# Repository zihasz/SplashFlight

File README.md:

# SplashFlight

SplashFlight is an all-in-one UAV control system designed from scratch, including a quadcopter control board, a general UAV control board, and software.

## Progress

### Hardware

-   [x] General UAV control board
-   [x] Quad-copter control board
-   [ ] PWM extension board
-   [ ] RF extension board
-   [ ] USB dongle - GPS
-   [ ] USB dongle - RF

### Software

-   [ ] Firmware for general UAV board
-   [ ] Firmware for quad-copter board
-   [ ] Ground control station software
-   [ ] Multi-OS Drivers for USB dongles

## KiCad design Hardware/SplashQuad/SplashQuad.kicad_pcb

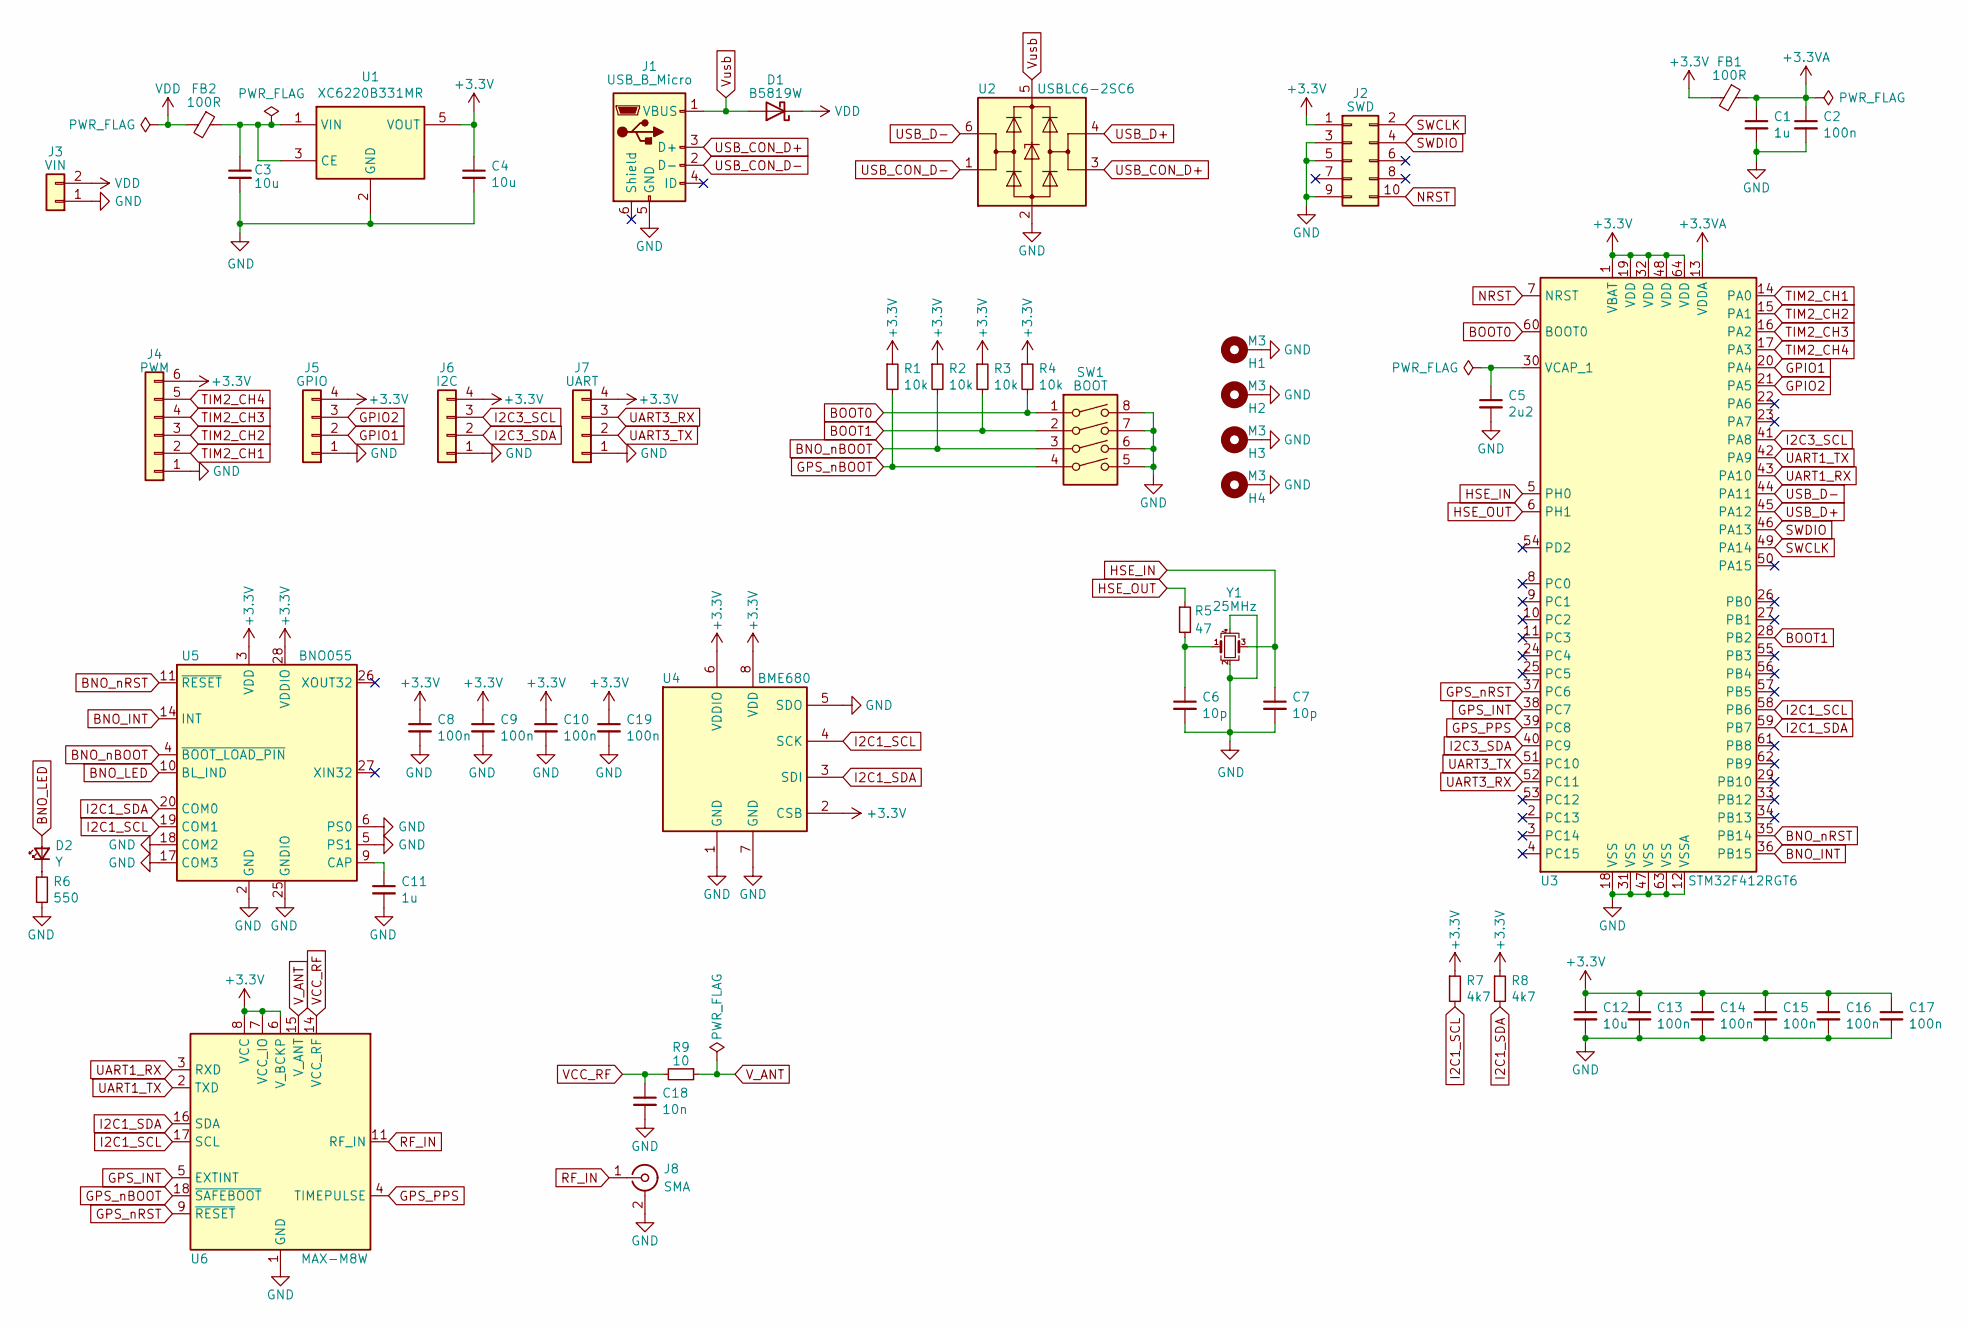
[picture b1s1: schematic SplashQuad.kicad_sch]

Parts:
C1, C11: 1u; C_0402_1005Metric
C2, C8, C9, C10, C13, C14, C15, C16, C17, C19: 100n; C_0402_1005Metric
C3, C4, C12: 10u; C_0402_1005Metric
C5: 2u2; C_0402_1005Metric
C6, C7: 10p; C_0402_1005Metric
C18: 10n; C_0402_1005Metric
D1: B5819W; D_SOD-123
D2: Y; LED_0603_1608Metric
FB1, FB2: 100R; L_0603_1608Metric
H1, H2, H3, H4: M3; MountingHole_3.2mm_M3_Pad_Via
J1: USB_B_Micro; USB_Micro-B_Molex-105017-0001
J2: SWD; PinHeader_2x05_P1.27mm_Vertical
J3: VIN; Molex_PicoBlade_53048-0210_1x02_P1.25mm_Horizontal
J4: PWM; Molex_PicoBlade_53048-0610_1x06_P1.25mm_Horizontal
J5: GPIO; Molex_PicoBlade_53048-0410_1x04_P1.25mm_Horizontal
J6: I2C; Molex_PicoBlade_53048-0410_1x04_P1.25mm_Horizontal
J7: UART; Molex_PicoBlade_53048-0410_1x04_P1.25mm_Horizontal
J8: SMA; SMA_Samtec_SMA-J-P-X-ST-EM1_EdgeMount
R1, R2, R3, R4: 10k; R_0402_1005Metric
R5: 47; R_0402_1005Metric
R6: 550; R_0402_1005Metric
R7, R8: 4k7; R_0402_1005Metric
R9: 10; R_0402_1005Metric
SW1: BOOT; SW_DIP_SPSTx04_Slide_Omron_A6H-4101_W6.15mm_P1.27mm
U1: XC6220B331MR; SOT-23-5
U2: USBLC6-2SC6; SOT-23-6
U3: STM32F412RGT6; LQFP-64_10x10mm_P0.5mm
U4: BME680; Bosch_LGA-8_3x3mm_P0.8mm_ClockwisePinNumbering
U5: BNO055; LGA-28_5.2x3.8mm_P0.5mm
U6: MAX-M8W; ublox_MAX
Y1: 25MHz; Crystal_SMD_3225-4Pin_3.2x2.5mm

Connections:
+3.3VA: C1.1, C2.1, FB1.1, U3.13 (VDDA)
+3V3: C4.1, C8.1, C9.1, C10.1, C12.1, C13.1, C14.1, C15.1, C16.1, C17.1, C19.1, FB1.2, J2.1, J4.6, J5.4, J6.4, J7.4, R1.1, R2.1, R3.1, R4.1, R7.1, R8.1, U1.5 (VOUT), U3.1 (VBAT), U3.19 (VDD), U3.32 (VDD), U3.48 (VDD), U3.64 (VDD), U4.2 (CSB), U4.6 (VDDIO), U4.8 (VDD), U5.3 (VDD), U5.28 (VDDIO), U6.6 (V_BCKP), U6.7 (VCC_IO), U6.8 (VCC)
BNO_INT: U3.36 (PB15), U5.14 (INT)
BNO_LED: D2.2 (A), U5.10 (BL_IND)
BNO_nBOOT: R2.2, SW1.3, U5.4 (~BOOT_LOAD_PIN)
BNO_nRST: U3.35 (PB14), U5.11 (~RESET)
BOOT0: R4.2, SW1.1, U3.60 (BOOT0)
BOOT1: R3.2, SW1.2, U3.28 (PB2)
GND: C1.2, C2.2, C3.2, C4.2, C5.2, C6.2, C7.2, C8.2, C9.2, C10.2, C11.2, C12.2, C13.2, C14.2, C15.2, C16.2, C17.2, C18.2, C19.2, H1.1, H2.1, H3.1, H4.1, J1.5 (GND), J2.3, J2.5, J2.9, J3.1, J4.1, J5.1, J6.1, J7.1, J8.2 (Ext), R6.2, SW1.5, SW1.6, SW1.7, SW1.8, U1.2 (GND), U2.2 (GND), U3.12 (VSSA), U3.18 (VSS), U3.31 (VSS), U3.47 (VSS), U3.63 (VSS), U4.1 (GND), U4.5 (SDO), U4.7 (GND), U5.2 (GND), U5.5 (PS1), U5.6 (PS0), U5.15 (GNDIO), U5.16 (GNDIO), U5.17 (COM3), U5.18 (COM2), U5.25 (GNDIO), U6.1 (GND), U6.10 (GND), U6.12 (GND), Y1.2, Y1.4
GPIO1: J5.2, U3.20 (PA4)
GPIO2: J5.3, U3.21 (PA5)
GPS_INT: U3.38 (PC7), U6.5 (EXTINT)
GPS_PPS: U3.39 (PC8), U6.4 (TIMEPULSE)
GPS_nBOOT: R1.2, SW1.4, U6.18 (~SAFEBOOT)
GPS_nRST: U3.37 (PC6), U6.9 (~RESET)
HSE_IN: C7.1, U3.5 (PH0), Y1.3
HSE_OUT: R5.1, U3.6 (PH1)
I2C1_SCL: R7.2, U3.58 (PB6), U4.4 (SCK), U5.19 (COM1), U6.17 (SCL)
I2C1_SDA: R8.2, U3.59 (PB7), U4.3 (SDI), U5.20 (COM0), U6.16 (SDA)
I2C3_SCL: J6.3, U3.41 (PA8)
I2C3_SDA: J6.2, U3.40 (PC9)
NRST: J2.10, U3.7 (NRST)
unnamed: C3.1, FB2.1, U1.1 (VIN), U1.3 (CE)
unnamed: C5.1, U3.30 (VCAP_1)
unnamed: C6.1, R5.2, Y1.1
unnamed: C11.1, U5.9 (CAP)
unnamed: D2.1 (K), R6.1
RF_IN: J8.1 (In), U6.11 (RF_IN)
SWCLK: J2.2, U3.49 (PA14)
SWDIO: J2.4, U3.46 (PA13)
TIM2_CH1: J4.2, U3.14 (PA0)
TIM2_CH2: J4.3, U3.15 (PA1)
TIM2_CH3: J4.4, U3.16 (PA2)
TIM2_CH4: J4.5, U3.17 (PA3)
UART1_RX: U3.43 (PA10), U6.3 (RXD)
UART1_TX: U3.42 (PA9), U6.2 (TXD)
UART3_RX: J7.3, U3.52 (PC11)
UART3_TX: J7.2, U3.51 (PC10)
USB_CON_D+: J1.3 (D+), U2.3 (I/O2)
USB_CON_D-: J1.2 (D-), U2.1 (I/O1)
USB_D+: U2.4 (I/O2), U3.45 (PA12)
USB_D-: U2.6 (I/O1), U3.44 (PA11)
VCC_RF: C18.1, R9.2, U6.14 (VCC_RF)
VDD: D1.1 (K), FB2.2, J3.2
V_ANT: R9.1, U6.15 (V_ANT)
Vusb: D1.2 (A), J1.1 (VBUS), U2.5 (VBUS)

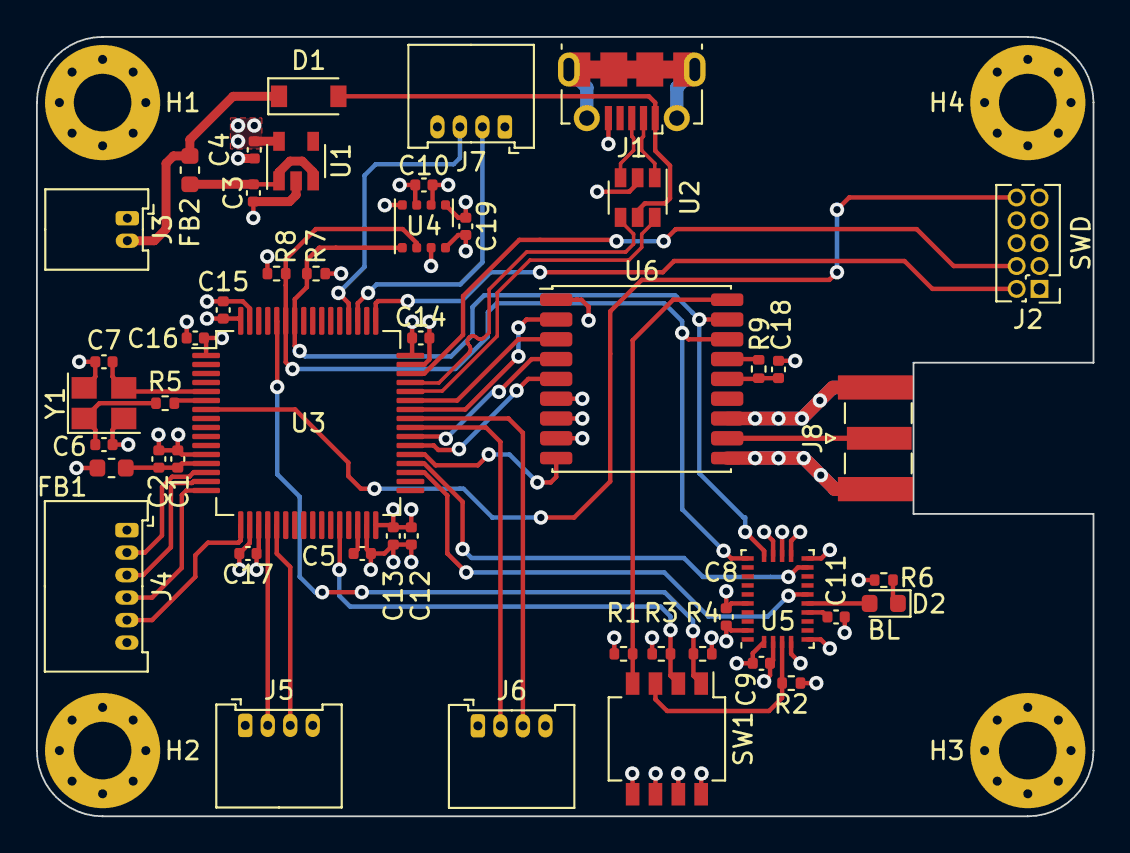
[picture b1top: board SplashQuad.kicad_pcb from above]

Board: 4 copper layers, 58.7 x 43.3 mm, 52 parts (0 on the bottom side), 46 nets.

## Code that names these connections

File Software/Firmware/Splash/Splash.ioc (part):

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Mcu.Name=STM32H753VITx
Mcu.Package=LQFP100
Mcu.UserName=STM32H753VITx
PA0.Mode=IN16-Differential
PA0.Signal=ADC1_INP16
PA1.Mode=IN16-Differential
PA1.Signal=ADC1_INN16
PA11.GPIOParameters=GPIO_Label
PA11.GPIO_Label=USB_DN
PA11.Mode=Device_Only
PA11.Signal=USB_OTG_FS_DM
PA12.GPIOParameters=GPIO_Label
PA12.GPIO_Label=USB_DP
PA12.Mode=Device_Only
PA12.Signal=USB_OTG_FS_DP
PA13\ (JTMS/SWDIO).GPIOParameters=GPIO_Label
PA13\ (JTMS/SWDIO).GPIO_Label=SWDIO
PA13\ (JTMS/SWDIO).Mode=Serial_Wire
PA13\ (JTMS/SWDIO).Signal=DEBUG_JTMS-SWDIO
PA14\ (JTCK/SWCLK).GPIOParameters=GPIO_Label
PA14\ (JTCK/SWCLK).GPIO_Label=SWCLK
PA14\ (JTCK/SWCLK).Mode=Serial_Wire
PA14\ (JTCK/SWCLK).Signal=DEBUG_JTCK-SWCLK
PA2.Signal=ADCx_INP14
PA3.Signal=ADCx_INP15
PA4.Signal=COMP_DAC11_group
PA5.Signal=COMP_DAC12_group
PA8.Mode=I2C
PA8.Signal=I2C3_SCL
PB10.Mode=I2C
PB10.Signal=I2C2_SCL
PB11.Mode=I2C
PB11.Signal=I2C2_SDA
PB12.Mode=Asynchronous
PB12.Signal=UART5_RX
PB13.Mode=Asynchronous
PB13.Signal=UART5_TX
PB14.Mode=Multiprocessor_communication
PB14.Signal=USART1_TX
PB15.Mode=Multiprocessor_communication
PB15.Signal=USART1_RX
PB3\ (JTDO/TRACESWO).Mode=Full_Duplex_Master
PB3\ (JTDO/TRACESWO).Signal=SPI1_SCK
PB4\ (NJTRST).Mode=Full_Duplex_Master
PB4\ (NJTRST).Signal=SPI1_MISO
PB5.Mode=Full_Duplex_Master
PB5.Signal=SPI1_MOSI
PB6.GPIOParameters=GPIO_Label
PB6.GPIO_Label=BME_nCS
PB6.Signal=GPIO_Output
PB7.GPIOParameters=GPIO_Label
PB7.GPIO_Label=ADC_nCS
PB7.Signal=GPIO_Output
PB8.Mode=I2C
PB8.Signal=I2C1_SCL
PB9.Mode=I2C
PB9.Signal=I2C1_SDA
PC10.Mode=Asynchronous
PC10.Signal=UART4_TX
PC11.Mode=Asynchronous
PC11.Signal=UART4_RX
PC3_C.Signal=SPI2_MOSI
PC6.Mode=Asynchronous
PC6.Signal=USART6_TX
PC7.Mode=Asynchronous
PC7.Signal=USART6_RX
PC9.Mode=I2C
PC9.Signal=I2C3_SDA
PD1.Signal=GPIO_Input
PD12.Mode=I2C
PD12.Signal=I2C4_SCL
PD13.Mode=I2C
PD13.Signal=I2C4_SDA
PD2.Signal=GPIO_Input
PD3.Signal=GPIO_Output
PD4.Signal=GPIO_Output
PD5.Mode=Asynchronous
PD5.Signal=USART2_TX
PD6.Mode=Asynchronous
PD6.Signal=USART2_RX
PD7.GPIOParameters=GPIO_Label
PD7.GPIO_Label=ADC_nDRDY
PD7.Signal=GPIO_Input
PD8.Mode=Asynchronous
PD8.Signal=USART3_TX
PD9.Mode=Asynchronous
PD9.Signal=USART3_RX
PE0.GPIOParameters=GPIO_Label
PE0.GPIO_Label=IMU_INT
PE0.Signal=GPIO_Output
PE1.GPIOParameters=GPIO_Label
PE1.GPIO_Label=IMU_nRST
PE1.Signal=GPIO_Output
PE11.Signal=S_TIM1_CH2
PE13.Signal=S_TIM1_CH3
PE14.Signal=S_TIM1_CH4
PE7.Mode=Asynchronous
PE7.Signal=UART7_RX
PE8.Mode=Asynchronous
PE8.Signal=UART7_TX
PE9.Signal=S_TIM1_CH1
PH0-OSC_IN\ (PH0).GPIOParameters=GPIO_Label
PH0-OSC_IN\ (PH0).GPIO_Label=HSE_IN
PH0-OSC_IN\ (PH0).Mode=HSE-External-Oscillator
PH0-OSC_IN\ (PH0).Signal=RCC_OSC_IN
PH1-OSC_OUT\ (PH1).GPIOParameters=GPIO_Label
PH1-OSC_OUT\ (PH1).GPIO_Label=HSE_OUT
PH1-OSC_OUT\ (PH1).Mode=HSE-External-Oscillator
PH1-OSC_OUT\ (PH1).Signal=RCC_OSC_OUT
RCC.HSE_VALUE=16000000
RCC.SYSCLKFreq_VALUE=64000000
board=custom

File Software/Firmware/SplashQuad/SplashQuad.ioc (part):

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Mcu.Name=STM32F412R(E-G)Tx
Mcu.Package=LQFP64
Mcu.UserName=STM32F412RGTx
PA0.Signal=S_TIM2_CH1_ETR
PA1.Signal=S_TIM2_CH2
PA10.Mode=Asynchronous
PA10.Signal=USART1_RX
PA11.Mode=Device_Only
PA11.Signal=USB_OTG_FS_DM
PA12.Mode=Device_Only
PA12.Signal=USB_OTG_FS_DP
PA13.Mode=Serial_Wire
PA13.Signal=SYS_JTMS-SWDIO
PA14.Mode=Serial_Wire
PA14.Signal=SYS_JTCK-SWCLK
PA2.Signal=S_TIM2_CH3
PA3.Signal=S_TIM2_CH4
PA4.Signal=ADCx_IN4
PA5.Signal=ADCx_IN5
PA8.Mode=I2C
PA8.Signal=I2C3_SCL
PA9.Mode=Asynchronous
PA9.Signal=USART1_TX
PB6.Mode=I2C
PB6.Signal=I2C1_SCL
PB7.Mode=I2C
PB7.Signal=I2C1_SDA
PC10.Mode=Asynchronous
PC10.Signal=USART3_TX
PC11.Mode=Asynchronous
PC11.Signal=USART3_RX
PC9.Mode=I2C
PC9.Signal=I2C3_SDA
PH0\ -\ OSC_IN.GPIOParameters=GPIO_Label
PH0\ -\ OSC_IN.GPIO_Label=HSE_IN
PH0\ -\ OSC_IN.Mode=HSE-External-Oscillator
PH0\ -\ OSC_IN.Signal=RCC_OSC_IN
PH1\ -\ OSC_OUT.GPIOParameters=GPIO_Label
PH1\ -\ OSC_OUT.GPIO_Label=HSE_OUT
PH1\ -\ OSC_OUT.Mode=HSE-External-Oscillator
PH1\ -\ OSC_OUT.Signal=RCC_OSC_OUT
RCC.HSE_VALUE=25000000
RCC.SYSCLKFreq_VALUE=96195652.17391303
RCC.SYSCLKSource=RCC_SYSCLKSOURCE_PLLCLK
board=custom

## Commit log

2021-12-21 Adds README for Splash hardware
